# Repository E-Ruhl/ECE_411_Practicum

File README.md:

# ECE_411_Practicum
Project development

Check out these sites for getting an idea of what we might try

https://www.adafruit.com/product/3538
this is the IR Camera

https://www.adafruit.com/product/684
this is the OLED screen

http://www.microchip.com/wwwproducts/en/ATmega328
this is the microcontroller

http://www.instructables.com/id/Arduino-Data-Glasses-for-My-Multimeter/
This is an instructable for a DIY Heads up display that actually has decent documentation

https://www.autodesk.com/education/free-software/eagle#
You'll need to go here to download the educational version of Eagle Cad

Also because I got super excited and already ordered most of the material for the thermal overlay augmented reality HUD, if you're into that idea (because I'm eventually doing it either way) then read up on Bicubic interpolation!!!

Other programs you might want to consider
Jupyter Notebook- Allows you to use basic Latex markdown and run python in an online application.

https://wwwspikenzielabs.com/Catalog/index.php?main_page=product_infor&products_id=614

We'll set up meeting notes on friday.

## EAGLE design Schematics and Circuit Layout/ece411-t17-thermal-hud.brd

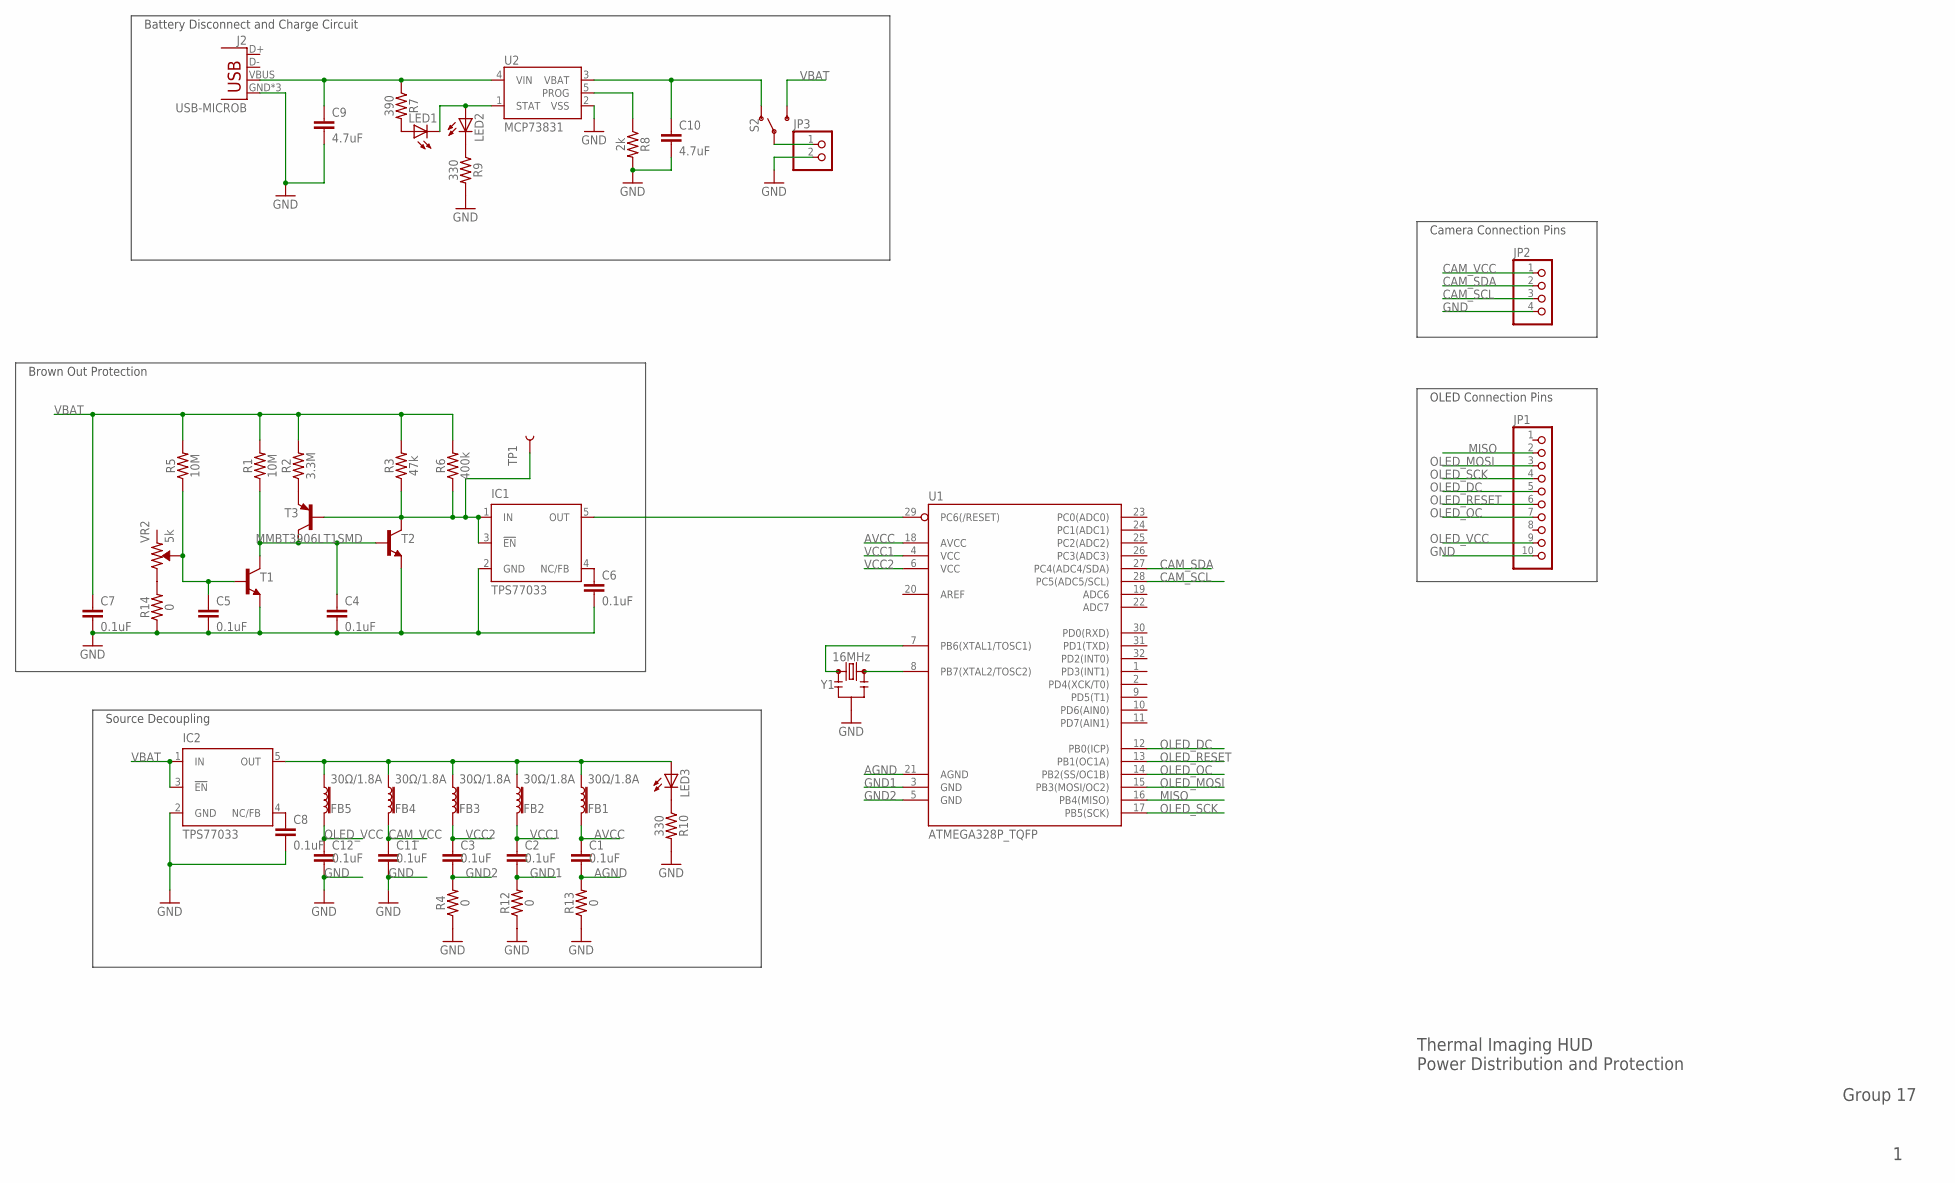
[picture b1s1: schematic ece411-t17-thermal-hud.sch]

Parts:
C1, C2, C3, C4, C5, C6, C7, C8, C11, C12: 0.1uF; 0603
C9, C10: 4.7uF; 0603
FB1, FB2, FB3, FB4, FB5: 30Ω/1.8A; 0603
IC1, IC2: TPS77033; SOT23-DBV
J2: USB-MICROB
JP1: PINHD-1X10/90; 1X10/90
JP2: PINHD-1X4/90; 1X04/90
JP3: PINHD-1X2/90; 1X02/90
LED1, LED2, LED3: LEDCHIPLED_0603; CHIPLED_0603
R1, R5: 10M; 0603
R2: 3.3M; 0603
R3: 47k; 0603
R4, R12, R13, R14: 0; 0603
R6: 400k; 0603
R7: 390; 0603
R8: 2k; 0603
R9, R10: 330; 0603
S2: SWITCH-SPDT-PTH-11.6X4.0MM; SWITCH_SPDT_PTH_11.6X4.0MM
T1, T2: MMBT3904LT1-NPN-SOT23-BEC; SOT23-BEC
T3: MMBT3906LT1SMD; SOT23-BEC
TP1: TEST-POINT3X5; PAD.03X.05
U1: ATMEGA328P_TQFP; TQFP32-08
U2: MCP73831; SOT23-5
VR2: 5k; TRIMPOT-SMD-5MM
Y1: 16MHz; RESONATOR-SMD-3.2X1.3

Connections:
AGND: C1.2, R13.2, U1.21 (AGND)
AVCC: C1.1, FB1.2, U1.18 (AVCC)
CAM_SCL: JP2.3, U1.28 (PC5(ADC5/SCL))
CAM_SDA: JP2.2, U1.27 (PC4(ADC4/SDA))
CAM_VCC: C11.1, FB4.2, JP2.1
GND: C4.2, C5.2, C6.2, C7.2, C8.2, C9.2, C10.2, C11.2, C12.2, IC1.2 (GND), IC2.2 (GND), J2.GND, J2.MT1 (GND), J2.MT2 (GND), JP1.10, JP2.4, JP3.2, R4.1, R8.2, R9.2, R10.2, R12.1, R13.1, R14.1, T1.E, T2.E, U2.2 (VSS), Y1.2
GND1: C2.2, R12.2, U1.3 (GND)
GND2: C3.2, R4.2, U1.5 (GND)
LIPO_POS: JP3.1, S2.2
MISO: JP1.2, U1.16 (PB4(MISO))
unnamed: IC1.1 (IN), IC1.3 (!EN), R3.1, R6.1, T2.C, T3.B, TP1.P$1
unnamed: C5.1, R5.1, T1.B, VR2.B (WIPER)
unnamed: IC1.5 (OUT), U1.29 (PC6(/RESET))
unnamed: C4.1, R1.1, T1.C, T2.B, T3.C
unnamed: R2.1, T3.E
unnamed: LED1.C, LED2.A, U2.1 (STAT)
unnamed: C6.1, IC1.4 (NC/FB)
unnamed: FB1.1, FB2.1, FB3.1, FB4.1, FB5.1, IC2.5 (OUT), LED3.A
unnamed: C8.1, IC2.4 (NC/FB)
unnamed: LED1.A, R7.2
unnamed: C9.1, J2.VBUS, R7.1, U2.4 (VIN)
unnamed: R8.1, U2.5 (PROG)
unnamed: C10.1, S2.1 (O), U2.3 (VBAT)
unnamed: R14.2, VR2.C (CW)
unnamed: U1.7 (PB6(XTAL1/TOSC1)), Y1.1
unnamed: U1.8 (PB7(XTAL2/TOSC2)), Y1.3
unnamed: LED2.C, R9.1
unnamed: LED3.C, R10.1
OLED_DC: JP1.5, U1.12 (PB0(ICP))
OLED_MOSI: JP1.3, U1.15 (PB3(MOSI/OC2))
OLED_OC: JP1.7, U1.14 (PB2(SS/OC1B))
OLED_RESET: JP1.6, U1.13 (PB1(OC1A))
OLED_SCK: JP1.4, U1.17 (PB5(SCK))
OLED_VCC: C12.1, FB5.2, JP1.9
VBAT: C7.1, IC2.1 (IN), IC2.3 (!EN), R1.2, R2.2, R3.2, R5.2, R6.2, S2.3 (S)
VCC1: C2.1, FB2.2, U1.4 (VCC)
VCC2: C3.1, FB3.2, U1.6 (VCC)

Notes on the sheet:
Battery Disconnect and Charge Circuit
Brown Out Protection
Source Decoupling
Camera Connection Pins
OLED Connection Pins
Group 17
Thermal Imaging HUD Power Distribution and Protection

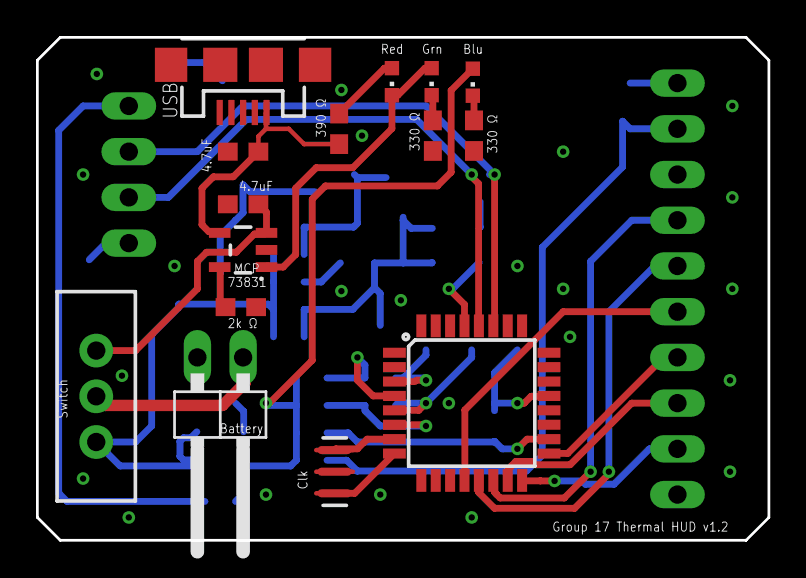
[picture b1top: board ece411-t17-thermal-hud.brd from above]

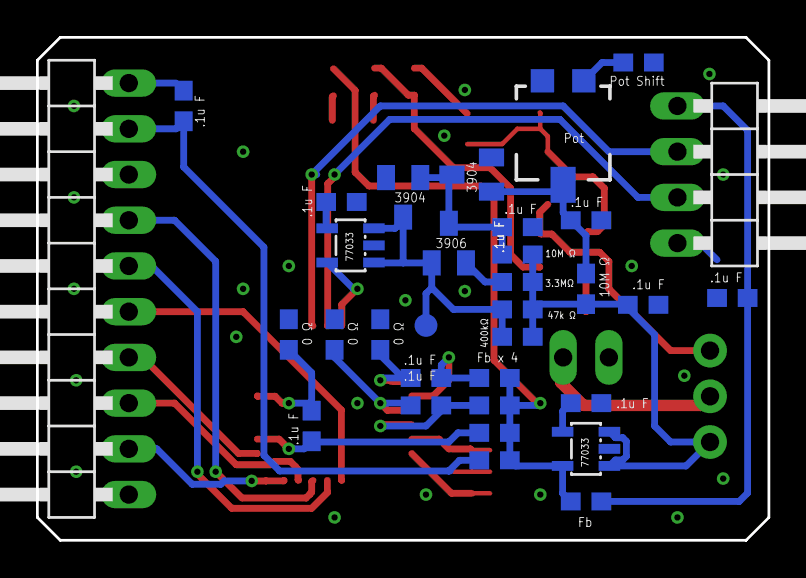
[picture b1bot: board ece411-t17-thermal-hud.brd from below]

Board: 2 copper layers, 40.6 x 27.9 mm, 48 parts (33 on the bottom side), 37 nets.

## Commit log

2017-10-09 finally ready
2017-10-10 This is our project ideas
2017-10-12 Documentation Files
2017-10-19 Create LICENSE
    MIT licence was chosen and added to the GitHub.
2017-10-20 Adafruit AMG8833 Thermal Camera Sensor Documentation
    Documentation for the Adafruit AMG8833 8x8 Thermal Camera Sensor that covers pinouts, wiring, testing, use and code libraries
2017-10-20 AMG88XX Technical Reference
    Technical Reference Document for the AMG88XX Infrared Array Sensor known as "Grid-EYE". Documentation contains characteristics, schematic and interfacing/use information for the AMG88XX
2017-10-20 Atmel ATmega 328 Datasheet
    Complete datasheet for the Atmel ATmega 328/P 8 bit AVR Microcontroller
2017-10-20 OLED Datasheet
    Technical reference document for the 96x64 RGB Dot Matrix OLED screen used in the design. Document contains design specifications and information on the SSD1331 Driver that is used by the device and 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
2017-10-20 Update README.md
    added links to website for OLED screen and microcontroller
2017-10-21 Create Arduino_PixelTest
    AMG8833 GridEYE 8x8 IR camera
2017-10-21 File was moved
2017-10-21 File was moved into a folder
2017-10-21 Test code for the SSD1331 using Arduino
    This code for a proof of concept using the SSD1331
2017-10-21 Adafruit_SSD1331.cpp for proof of concept
2017-10-21 Moved the Arduino test code for SSD1331
2017-10-21 File was moved to Arduino code folder
2017-10-21 Cpp file for proof of concept for SSD1331
2017-10-21 File moved to another folder
2017-10-21 Header file for the SSD1331 for proof of concept
2017-10-21 Datasheet for the SSD1331 OLED controller
2017-10-21 Moved to another folder
2017-10-21 Arduino cpp for proof of concept for AMG8833
2017-10-21 File was moved to another folder
2017-10-21 Header file for the AMG8833 for proof of concept
2017-10-21 Cpp file for the AMG8833 for proof of concept
2017-10-21 Add files via upload
    Pinout Diagram for Atmel ATmega328/P TQFP package
2017-10-21 Add files via upload
    Pinout diagram for Atmel ATmega328p DIP
2017-10-21 Description and Requirements for Practicum
    This document contains all of the requirements for our ECE411 Practicum Project
2017-10-21 Weekly Progress Report
2017-10-21 Create sch file for AMG8833
2017-10-21 Create a brd file for the AMG8833
2017-10-21 Create brd file for OLED screen
2017-10-21 Create sch file for the OLED screen
2017-10-26 Power and charging systems
2017-11-02 Added project timeline
2017-11-02 final Schematic
2017-11-03 Delete Atmel-42735-8-bit-AVR-Microcontroller-ATmega328-328P_Datasheet.pdf
    removed in order to relocate and clean up main page
2017-11-03 Delete ATMEGA328P-PU-BOOT - Layout01.jpg
    removed in order to relocate and clean up main page
2017-11-03 Delete atmega328-tqfp-arduino-pinout.jpg
    removed in order to relocate and clean up main page
2017-11-03 Atmel Atmega328P Datasheet
    The complete datasheet for the Atmel Atmega328P microprocessor
2017-11-03 Delete ReadMe.me
    Deleted ReadMe.me in order to recreate ReadMe file
2017-11-05 Adafruit OLED Breakout board file
2017-11-05 Adafruit OLED breakout schematic file
2017-11-05 Wrong board file
2017-11-05 Wrong schematic file
2017-11-07 Pre Layout
2017-11-08 pre-Layout
2017-11-09 Block diagram of the design
2017-11-10 altered board to fit OSH DRS
2017-11-10 PDF version of the project calendar
2017-11-10 Place project calendar into folder
2017-11-10 File was moved to Project Calendar folder
2017-11-10 Moved to the Project Calendar folder
2017-11-10 Add files via upload
    Nearest Neighbor averaging upscale
2017-11-13 Prototype Structure
2017-11-13 Added weekly progress reports
2017-11-14 Modification to thermal HUD code
    Changes from float variables to uint8_t variables
2017-11-14 Tried to fix errors to thermal HUD code
    The fixs applied fixed some of the errors, but more still need to be
    fixed.
2017-11-14 Cut unused functions from AMG88xx.cpp
    Functions that are not used by the readPixel function. The read pixel function is the only function being called by our main program file.
2017-11-14 Cut unused functions from the AMG88xx.h
    Removed unused function prototypes from the header file to reflect changes made to AMG88xx.cpp file.
2017-11-15 Update Thermal_HUD_bicubic.ino
    Multiple methods of selecting a color were added
2017-11-15 Delete interpolation.cpp
    functions were moved to main .ino file
2017-11-15 Delete Thermal_HUD.ino
    no longer trying to implement nearest neighbor average as an interpolation method
2017-11-15 Rename Thermal Imaging HUD code/Thermal_HUD_bicubic.ino to Thermal Imaging HUD code/Thermal_HUD_bicubic/Thermal_HUD_bicubic.ino
2017-11-15 Added prototyping photos
2017-11-15 Delete Thermal_HUD_bicubic.ino
    Odd merge issues leading to compilation errors
2017-11-16 Osh subit
2017-11-16 Changes for optimization
    Minor changes were made to optimize the code
2017-11-17 Added this weeks progress report
2017-11-17 Rename MeetingNotes_WPRs/Eric/Week 10_13_17 thru 10_19_17.txt to MeetingNotes_WPRs/WPR/Eric Ruhl/Week 10_13_17 thru 10_19_17.txt
2017-11-17 Rename MeetingNotes_WPRs/Eric/Week 10_20_17 thru 10_26_17.txt to MeetingNotes_WPRs/WPR/Eric Ruhl/Week 10_20_17 thru 10_26_17.txt
2017-11-17 Rename MeetingNotes_WPRs/Eric/Week 10_27_17 thru 11_2_17.txt to MeetingNotes_WPRs/WPR/Eric Ruhl/Week 10_27_17 thru 11_2_17.txt
2017-11-17 Rename MeetingNotes_WPRs/Eric/Week 10_6_17 thru 10_13_17.txt to MeetingNotes_WPRs/WPR/Eric Ruhl/Week 10_6_17 thru 10_13_17.txt
2017-11-17 Rename MeetingNotes_WPRs/Eric/Week 11_3_17 thru 11_9_17.txt to MeetingNotes_WPRs/WPR/Eric Ruhl/Week 11_3_17 thru 11_9_17.txt
2017-11-20 reorganized and added Test Sheet
2017-11-28 test doc
2017-11-28 Cut unused functions and added function definition
2017-11-30 Adjusted Structural Files
2017-12-01 test case update
2017-12-01 test plan submitted
2017-12-06 Added more photos to the project documentation
2017-12-06 Added the bill of materials

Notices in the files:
parts and their libraries:
SparkFun-Capacitors: Licensing: Creative Commons ShareAlike 4.0 International - https://creativecommons.org/licenses/by-sa/4.0
